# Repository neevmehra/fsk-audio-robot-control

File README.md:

# FSK Audio-Based Robot Control System

Real-time embedded communication system that transmits joystick commands over an acoustic channel using frequency shift keying (FSK), decodes received audio with ADC sampling and DFT-based frequency detection, and controls an RSLK robot.

## Overview

This project implements a wireless audio command system using two TM4C123 microcontrollers. The transmitter reads joystick input, maps each direction to a command, encodes the command into an audio signal, and outputs the waveform through a DAC and speaker. The receiver captures the transmitted signal through a microphone, samples it using an ADC, detects the dominant frequency, and drives an RSLK robot based on the decoded command.

The system was designed to operate in real time while remaining robust to noise and signal distortion in the acoustic channel.

## Features

* Joystick-controlled robot movement
* Acoustic command transmission using FSK tones
* DAC-generated sine wave output through speaker
* Microphone and ADC-based audio capture
* DFT-based frequency detection for command decoding
* FIFO buffering for real-time sample processing
* Interrupt-driven ADC sampling
* Stability filtering and thresholding for noise-tolerant decoding
* RSLK robot control for forward, backward, left, right, and stop commands

## System Architecture

1. Joystick input is read by the transmitter microcontroller.
2. The joystick direction is mapped to a command.
3. The command is encoded as an FSK audio tone.
4. The DAC generates the waveform and outputs it through a speaker.
5. The receiver microphone captures the transmitted audio.
6. The ADC samples the received signal.
7. A DFT-based decoder identifies the dominant frequency.
8. The decoded command is sent to the RSLK robot motor-control logic.

## Communication Protocol

The system uses frequency shift keying to represent command data as distinct audio tones. Each command is transmitted over the air through a speaker and decoded by identifying the dominant received frequency.

The receiver performs frequency-domain analysis using DFT magnitude calculations across expected command frequencies. Thresholding and stability checks help reject transient noise and prevent incorrect command execution.

## Technical Implementation

### Transmitter

* Reads joystick position using ADC inputs
* Applies directional mapping and deadband logic
* Converts commands into encoded audio tones
* Generates sine wave samples using a lookup table
* Outputs audio through a DAC and speaker circuit

### Receiver

* Samples microphone input using interrupt-driven ADC logic
* Removes DC offset from sampled audio
* Buffers samples using FIFO structures
* Computes DFT magnitudes for target frequencies
* Selects the dominant frequency based on magnitude and threshold checks
* Uses stability filtering before executing robot commands

### Robot Control

* Decoded commands control RSLK robot movement
* Supported commands include forward, backward, left, right, and stop
* The system runs within real-time constraints with sufficient CPU timing margin

## Hardware

* TM4C123 microcontrollers
* RSLK robot platform
* Joystick input module
* DAC output circuit
* Speaker
* Microphone receiver circuit
* Breadboarded analog interface circuitry
* Oscilloscope for waveform validation

## Software

* Embedded C
* Interrupt-driven ADC sampling
* DAC waveform generation
* FIFO buffering
* DFT-based frequency detection
* Command decoding and robot-control logic

## Testing

The system was tested at both the module and integration levels.

### Unit Testing

* Verified DAC sine wave output using oscilloscope traces
* Tested joystick ADC readings and command mapping
* Validated microphone ADC sampling
* Tested DFT frequency detection using known input tones
* Checked frame parsing and command decoding logic

### Integration Testing

* Verified end-to-end joystick-to-robot command transmission
* Tested real-time robot response to live joystick input
* Evaluated noise tolerance under background audio interference
* Measured communication reliability over increasing speaker-to-microphone distance
* Confirmed timing performance under real-time sampling constraints

## Results

* Successfully transmitted joystick commands over an acoustic channel
* Controlled an RSLK robot using decoded audio commands
* Maintained reliable command detection using DFT-based decoding
* Demonstrated real-time operation with interrupt-driven sampling and FIFO buffering
* Operated with tolerance to moderate environmental noise

## Repository Structure

```text
.
├── README.md
├── sw/                  # Embedded software
├── hw/                  # Hardware design files
├── Resources/           # Supporting resources
└── docs/                # Lab report and documentation
```

## Project Context

This project was completed for ECE445L and focused on real-time embedded systems, digital signal processing, hardware/software integration, and robotics control.

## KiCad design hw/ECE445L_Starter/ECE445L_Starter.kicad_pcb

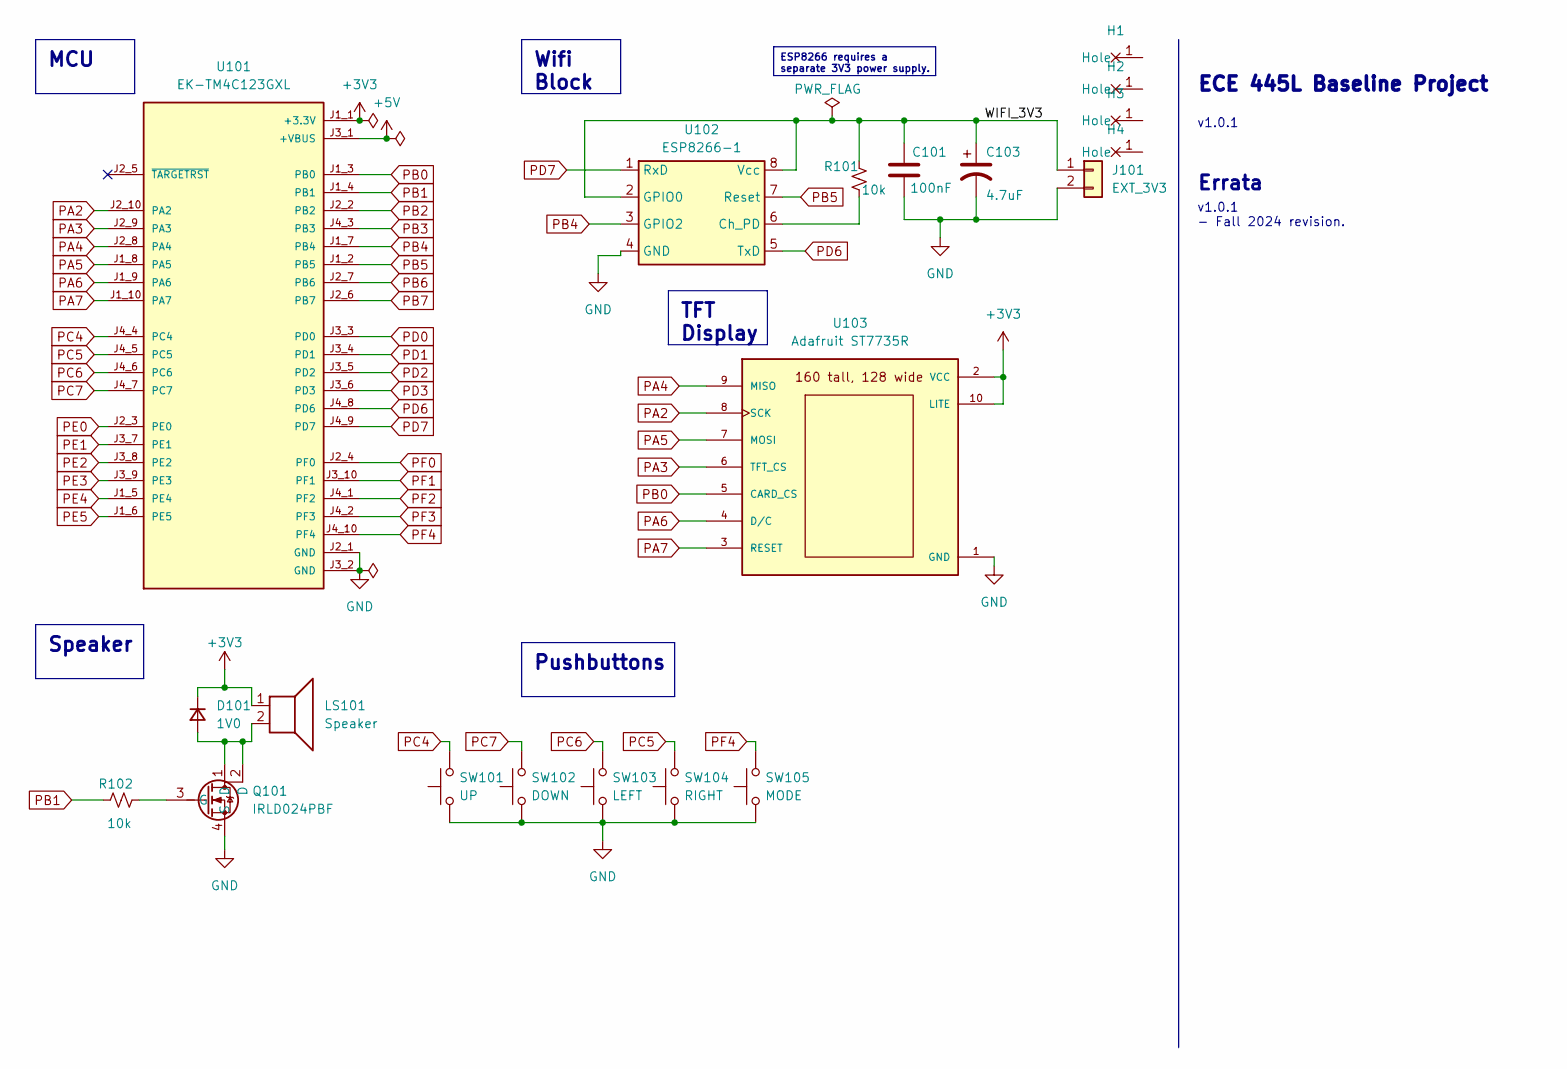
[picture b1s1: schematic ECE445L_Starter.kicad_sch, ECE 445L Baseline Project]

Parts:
C101: 100nF; C_Axial_200mil
C103: 4.7uF; CP_Radial_Tantal200mil
D101: 1V0; D_5W_P12.70mm_Horizontal
H1, H2, H3, H4: MountingHole_4_40
J101: EXT_3V3; Samtec_HPM-02-01-x-S_Straight_1x02_Pitch5.08mm
LS101: Speaker; PinHeader_1x02_P2.54mm_Vertical
Q101: IRLD024PBF; DIP920W60P254L490H457Q4N; Mouser Part Number 844-IRLD024PBF
R101, R102: 10k; R_Axial_DIN0204_L3.6mm_D1.6mm_P7.62mm_Horizontal
SW101: UP; SW_PUSH_6mm
SW102: DOWN; SW_PUSH_6mm
SW103: LEFT; SW_PUSH_6mm
SW104: RIGHT; SW_PUSH_6mm
SW105: MODE; SW_PUSH_6mm
U101: EK-TM4C123GXL; ti_EKTM4C123GXL
U102: ESP8266-1; PinHeader_2x04_P2.54mm_Vertical
U103: Adafruit ST7735R; adafruit_st7735r2

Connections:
+3V3: D101.1 (K), LS101.1, U101.J1_1 (+3.3V), U103.2 (VCC), U103.10 (LITE)
+5V: U101.J3_1 (+VBUS)
/WIFI_3V3: C101.1, C103.1, J101.1, R101.1, U102.2 (GPIO0), U102.8 (Vcc)
GND: C101.2, C103.2, J101.2, Q101.4 (S), SW101.1, SW102.1, SW103.1, SW104.1, SW105.1, U101.J2_1 (GND), U101.J3_2 (GND), U102.4 (GND), U103.1 (GND)
unnamed: D101.2 (A), LS101.2, Q101.1 (D), Q101.2 (D)
unnamed: Q101.3 (G), R102.2
unnamed: R101.2, U102.6 (Ch_PD)
PA2: U101.J2_10 (PA2), U103.8 (SCK)
PA3: U101.J2_9 (PA3), U103.6 (TFT_CS)
PA4: U101.J2_8 (PA4), U103.9 (MISO)
PA5: U101.J1_8 (PA5), U103.7 (MOSI)
PA6: U101.J1_9 (PA6), U103.4 (D/C)
PA7: U101.J1_10 (PA7), U103.3 (RESET)
PB0: U101.J1_3 (PB0), U103.5 (CARD_CS)
PB1: R102.1, U101.J1_4 (PB1)
PB2: U101.J2_2 (PB2)
PB3: U101.J4_3 (PB3)
PB4: U101.J1_7 (PB4), U102.3 (GPIO2)
PB5: U101.J1_2 (PB5), U102.7 (Reset)
PB6: U101.J2_7 (PB6)
PB7: U101.J2_6 (PB7)
PC4: SW101.2, U101.J4_4 (PC4)
PC5: SW104.2, U101.J4_5 (PC5)
PC6: SW103.2, U101.J4_6 (PC6)
PC7: SW102.2, U101.J4_7 (PC7)
PD0: U101.J3_3 (PD0)
PD1: U101.J3_4 (PD1)
PD2: U101.J3_5 (PD2)
PD3: U101.J3_6 (PD3)
PD6: U101.J4_8 (PD6), U102.5 (TxD)
PD7: U101.J4_9 (PD7), U102.1 (RxD)
PE0: U101.J2_3 (PE0)
PE1: U101.J3_7 (PE1)
PE2: U101.J3_8 (PE2)
PE3: U101.J3_9 (PE3)
PE4: U101.J1_5 (PE4)
PE5: U101.J1_6 (PE5)
PF0: U101.J2_4 (PF0)
PF1: U101.J3_10 (PF1)
PF2: U101.J4_1 (PF2)
PF3: U101.J4_2 (PF3)
PF4: SW105.2, U101.J4_10 (PF4)

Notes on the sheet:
MCU
ESP8266 requires a separate 3V3 power supply.
Speaker
Pushbuttons
TFT Display
Wifi Block
v1.0.1 - Fall 2024 revision.
ECE 445L Baseline Project
v1.0.1
Errata

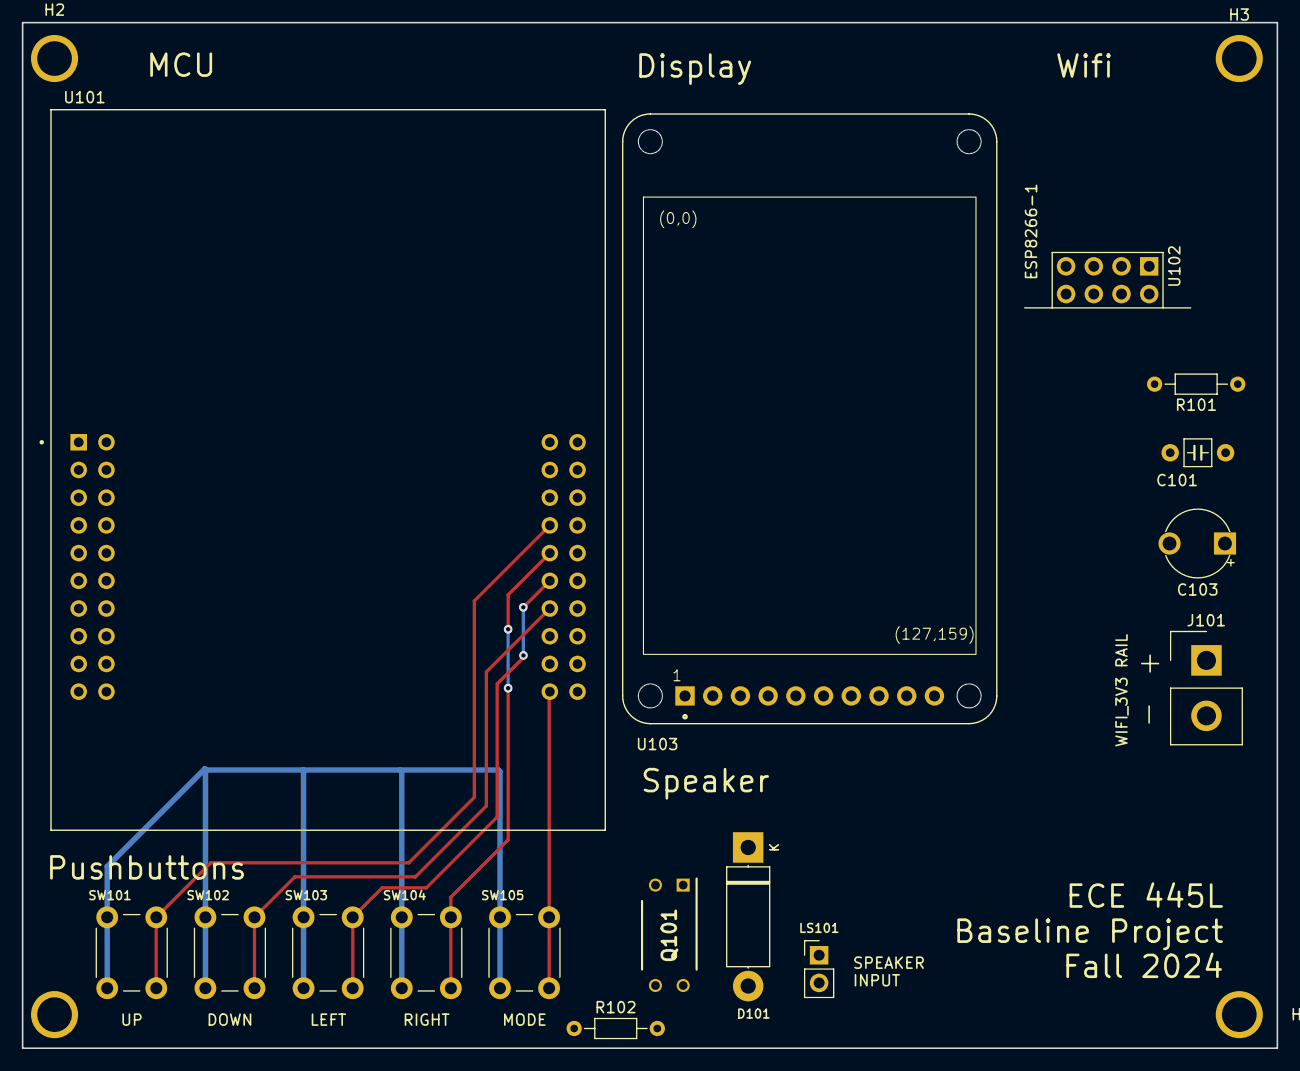
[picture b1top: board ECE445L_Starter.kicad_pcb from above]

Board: 2 copper layers, 115.0 x 94.0 mm, 20 parts (0 on the bottom side), 23 nets.

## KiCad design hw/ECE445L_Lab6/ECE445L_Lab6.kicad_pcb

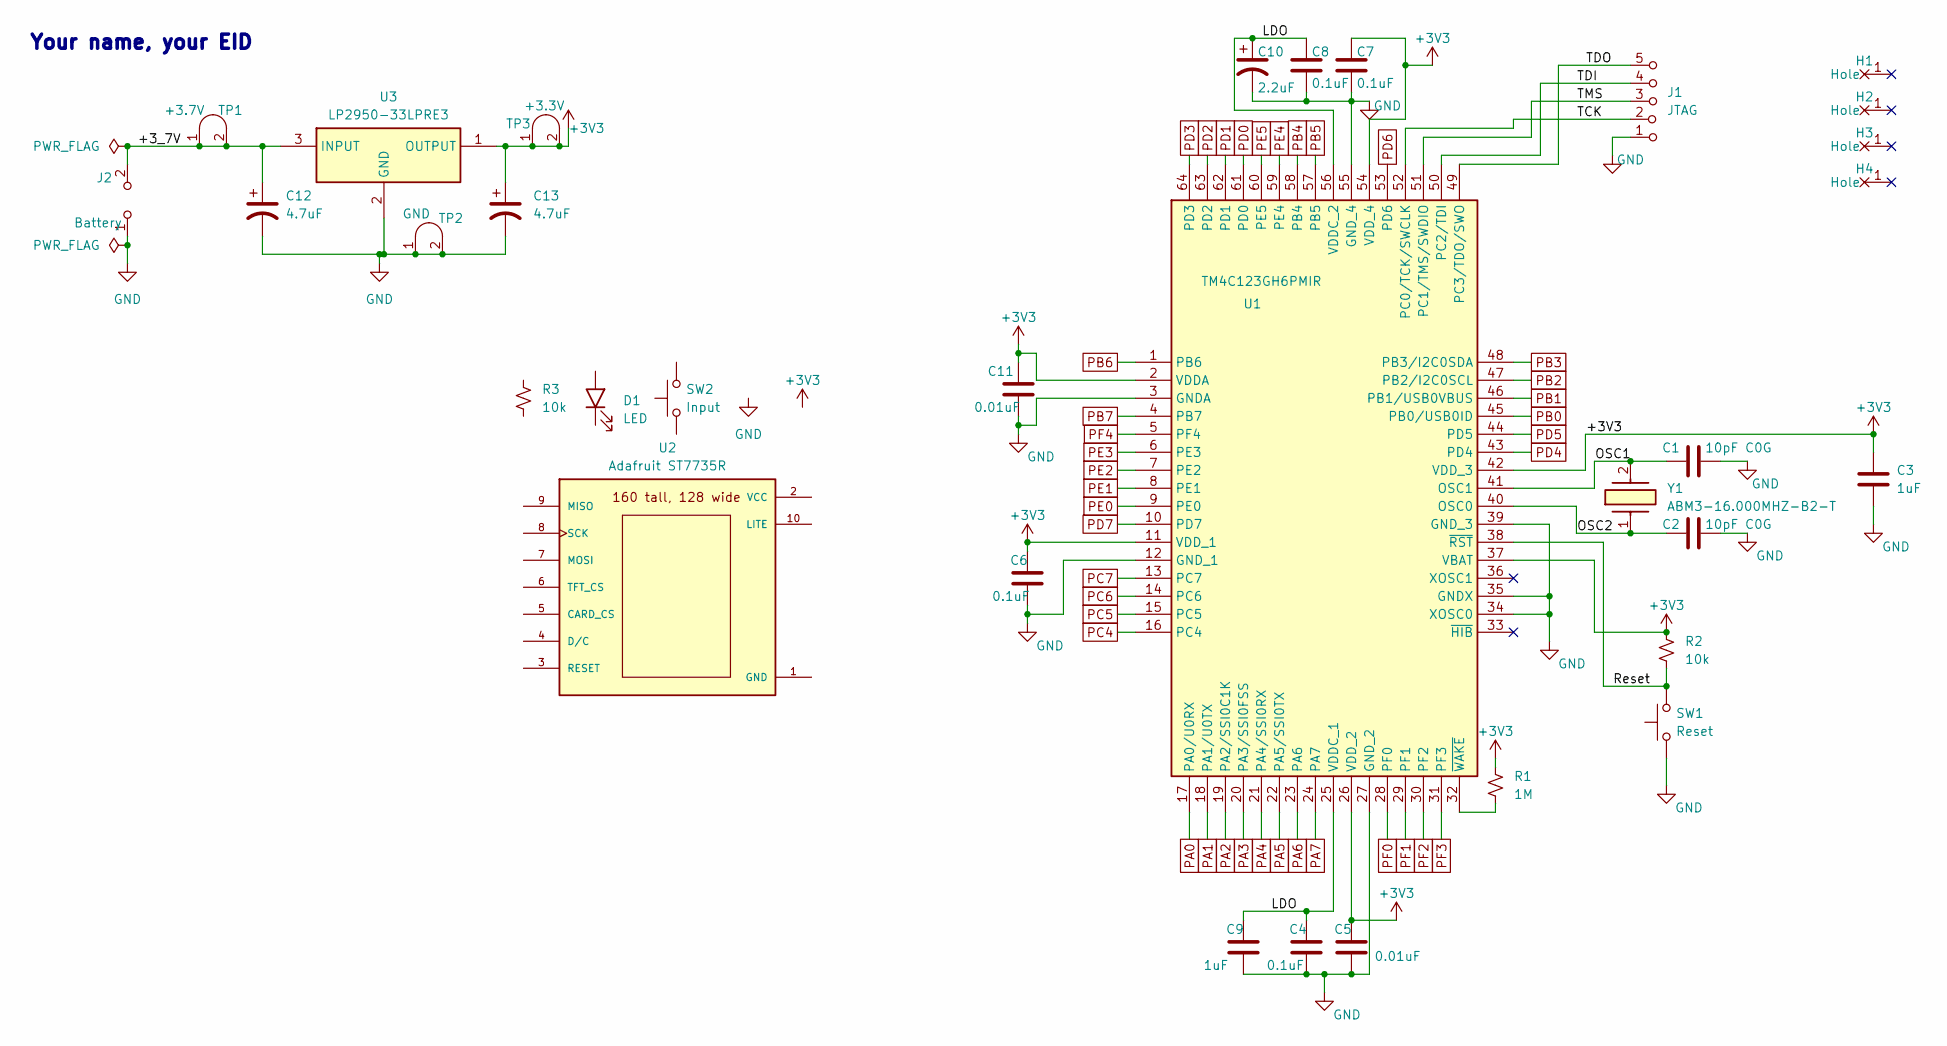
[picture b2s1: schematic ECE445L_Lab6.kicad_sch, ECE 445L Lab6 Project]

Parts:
C1, C2: 10pF C0G; C_Axial_200mil
C3, C9: 1uF; C_Axial_200mil
C4, C6, C7, C8: 0.1uF; C_Axial_200mil
C5, C11: 0.01uF; C_Axial_200mil
C10: 2.2uF; CP_Radial_Tantal200mil
C12, C13: 4.7uF; CP_Radial_Tantal200mil
D1: LED; LED_D5.0mm
H1, H2, H3, H4: MountingHole_4_40
J1: JTAG; PinHeader_1x05_P2.54mm_Vertical
J2: Battery; PinHeader_1x02_P2.54mm_Vertical
R1: 1M; R_Axial_DIN0204_L3.6mm_D1.6mm_P7.62mm_Horizontal
R2, R3: 10k; R_Axial_DIN0204_L3.6mm_D1.6mm_P7.62mm_Horizontal
SW1: Reset; SW_PUSH_6mm
SW2: Input; SW_PUSH_6mm
TP1: +3.7V; Testpoint_1x02_P2.54mm
TP2: GND; Testpoint_1x02_P2.54mm
TP3: +3.3V; Testpoint_1x02_P2.54mm
U1: TM4C123GH6PMIR; QFP50P1200X1200X160-64N; Mouser Part Number 595-TM4C123GH6PMIR
U2: Adafruit ST7735R; adafruit_st7735r2
U3: LP2950-33LPRE3; TL431CLPM; Mouser Part Number 595-LP2950-33LPRE3
Y1: ABM3-16.000MHZ-B2-T; ABM3; Mouser Part Number 815-ABM3-16-B2-T

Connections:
+3V3: C3.1, C5.1, C6.1, C7.1, C11.1, C13.1, R1.1, R2.1, TP3.1 (A), TP3.2 (B), U1.2 (VDDA), U1.11 (VDD_1), U1.26 (VDD_2), U1.37 (VBAT), U1.42 (VDD_3), U1.54 (VDD_4), U3.1 (OUTPUT)
/+3_7V: C12.1, J2.2 (B), TP1.1 (A), TP1.2 (B), U3.3 (INPUT)
/LDO: C4.1, C8.1, C9.1, C10.1, U1.25 (VDDC_1), U1.56 (VDDC_2)
/OSC1: C1.1, U1.41 (OSC1), Y1.2
/OSC2: C2.1, U1.40 (OSC0), Y1.1
/Reset: R2.2, SW1.2, U1.38 (~RST)
/TCK: J1.2 (B), U1.52 (PC0/TCK/SWCLK)
/TDI: J1.4 (C), U1.50 (PC2/TDI)
/TDO: J1.5 (C), U1.49 (PC3/TDO/SWO)
/TMS: J1.3 (C), U1.51 (PC1/TMS/SWDIO)
GND: C1.2, C2.2, C3.2, C4.2, C5.2, C6.2, C7.2, C8.2, C9.2, C10.2, C11.2, C12.2, C13.2, J1.1 (A), J2.1 (A), SW1.1, TP2.1 (A), TP2.2 (B), U1.3 (GNDA), U1.12 (GND_1), U1.27 (GND_2), U1.34 (XOSC0), U1.35 (GNDX), U1.39 (GND_3), U1.55 (GND_4), U3.2 (GND)
unnamed: R1.2, U1.32 (~WAKE)
PA0: U1.17 (PA0/U0RX)
PA1: U1.18 (PA1/U0TX)
PA2: U1.19 (PA2/SSI0C1K)
PA3: U1.20 (PA3/SSI0FSS)
PA4: U1.21 (PA4/SSI0RX)
PA5: U1.22 (PA5/SSI0TX)
PA6: U1.23 (PA6)
PA7: U1.24 (PA7)
PB0: U1.45 (PB0/USB0ID)
PB1: U1.46 (PB1/USB0VBUS)
PB2: U1.47 (PB2/I2C0SCL)
PB3: U1.48 (PB3/I2C0SDA)
PB4: U1.58 (PB4)
PB5: U1.57 (PB5)
PB6: U1.1 (PB6)
PB7: U1.4 (PB7)
PC4: U1.16 (PC4)
PC5: U1.15 (PC5)
PC6: U1.14 (PC6)
PC7: U1.13 (PC7)
PD0: U1.61 (PD0)
PD1: U1.62 (PD1)
PD2: U1.63 (PD2)
PD3: U1.64 (PD3)
PD4: U1.43 (PD4)
PD5: U1.44 (PD5)
PD6: U1.53 (PD6)
PD7: U1.10 (PD7)
PE0: U1.9 (PE0)
PE1: U1.8 (PE1)
PE2: U1.7 (PE2)
PE3: U1.6 (PE3)
PE4: U1.59 (PE4)
PE5: U1.60 (PE5)
PF0: U1.28 (PF0)
PF1: U1.29 (PF1)
PF2: U1.30 (PF2)
PF3: U1.31 (PF3)
PF4: U1.5 (PF4)

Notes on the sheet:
Your name, your EID

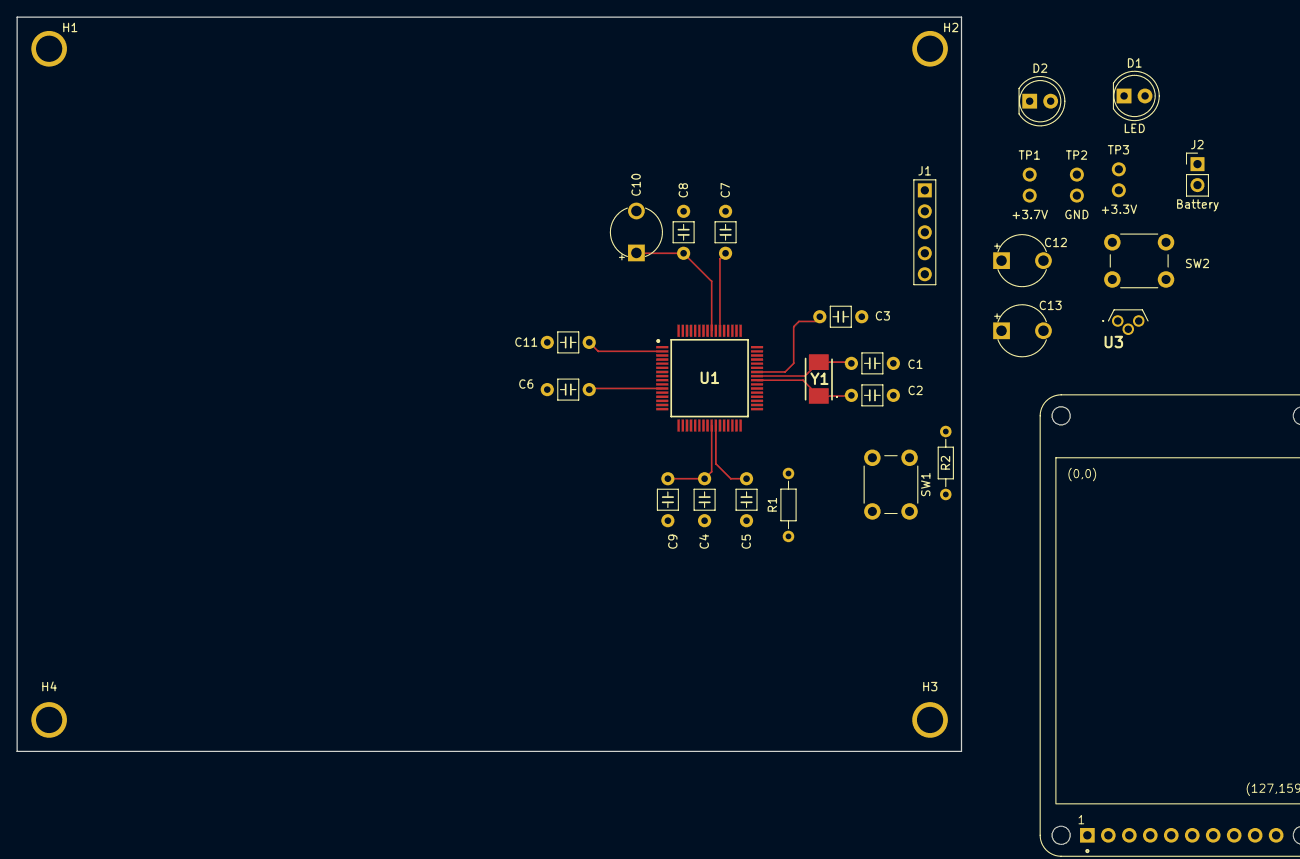
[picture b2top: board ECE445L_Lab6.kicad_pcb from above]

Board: 2 copper layers, 114.4 x 88.9 mm, 32 parts (0 on the bottom side), 12 nets.

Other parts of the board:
D2: LED; LED_D5.0mm

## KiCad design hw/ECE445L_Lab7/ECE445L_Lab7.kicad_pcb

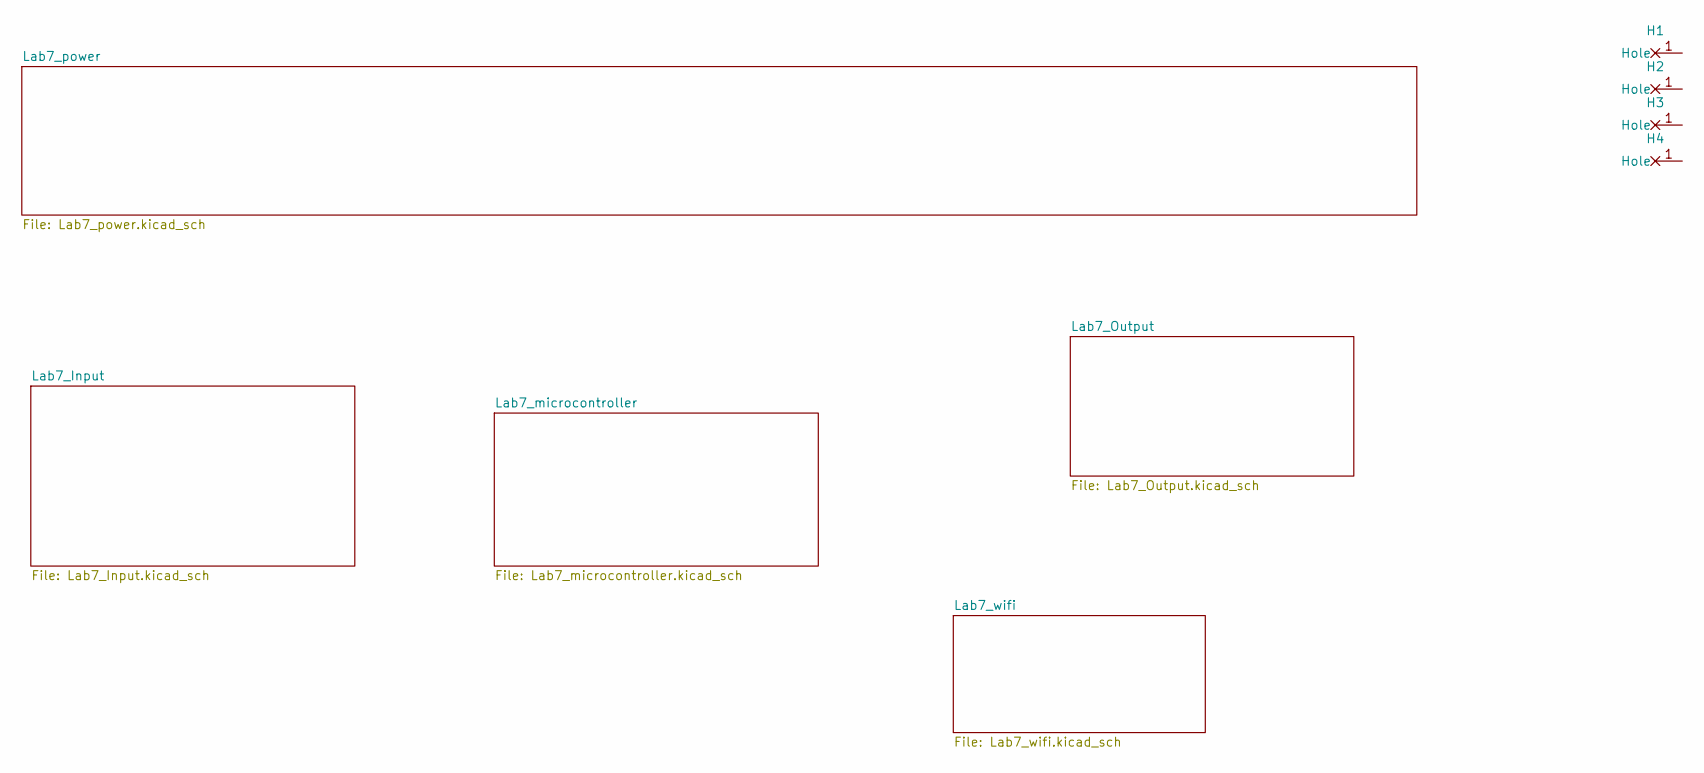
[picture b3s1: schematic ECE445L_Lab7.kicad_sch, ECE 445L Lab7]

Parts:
H1, H2, H3, H4: MountingHole_4_40

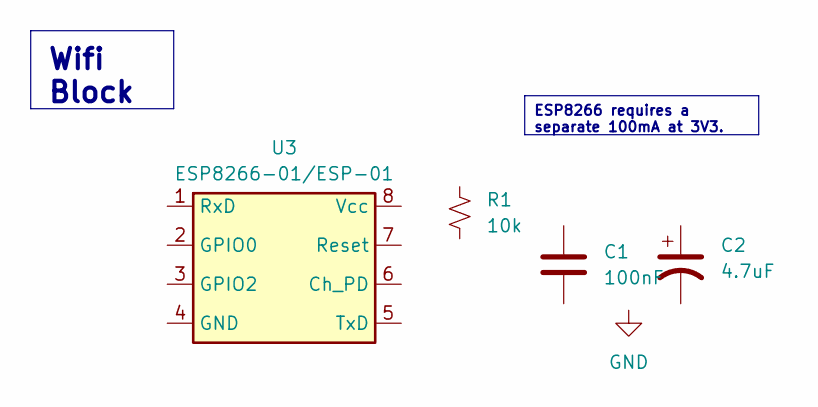
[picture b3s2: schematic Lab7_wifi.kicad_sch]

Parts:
C1: 100nF; C_Axial_200mil
C2: 4.7uF; CP_Radial_Tantal200mil
R1: 10k; R_Axial_DIN0204_L3.6mm_D1.6mm_P7.62mm_Horizontal
U3: ESP8266-01/ESP-01; PinHeader_2x04_P2.54mm_Vertical

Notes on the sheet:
ESP8266 requires a separate 100mA at 3V3.
Wifi Block

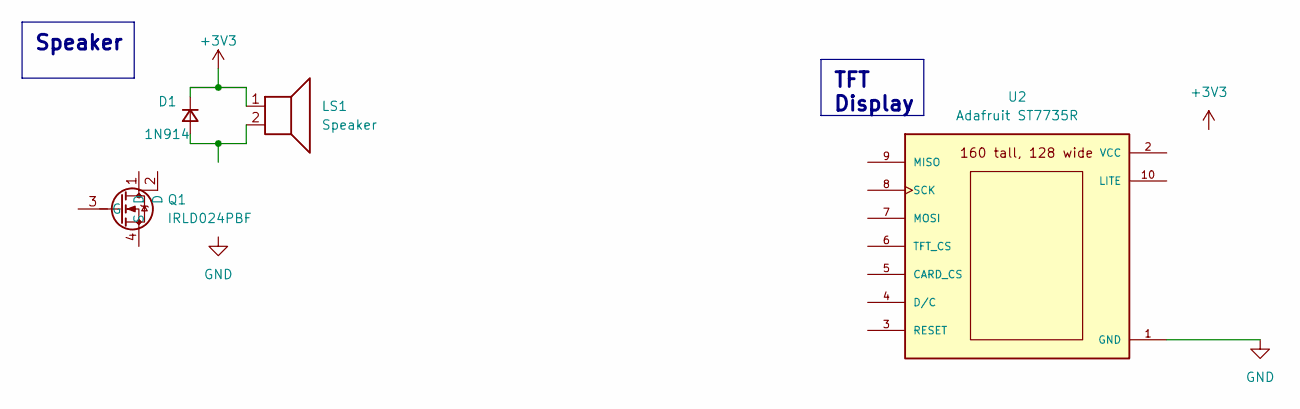
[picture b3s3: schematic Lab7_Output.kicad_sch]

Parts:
D1: 1N914; D_P6.35mm_Horizontal
LS1: Speaker; PinHeader_1x02_P2.54mm_Vertical
Q1: IRLD024PBF; DIP920W60P254L490H457Q4N; Mouser Part Number 844-IRLD024PBF
U2: Adafruit ST7735R; adafruit_st7735r2

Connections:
+3V3: D1.1 (K), LS1.1; also elsewhere on the board
GND: U2.1 (GND); also elsewhere on the board
unnamed: D1.2 (A), LS1.2

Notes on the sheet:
TFT Display
Speaker

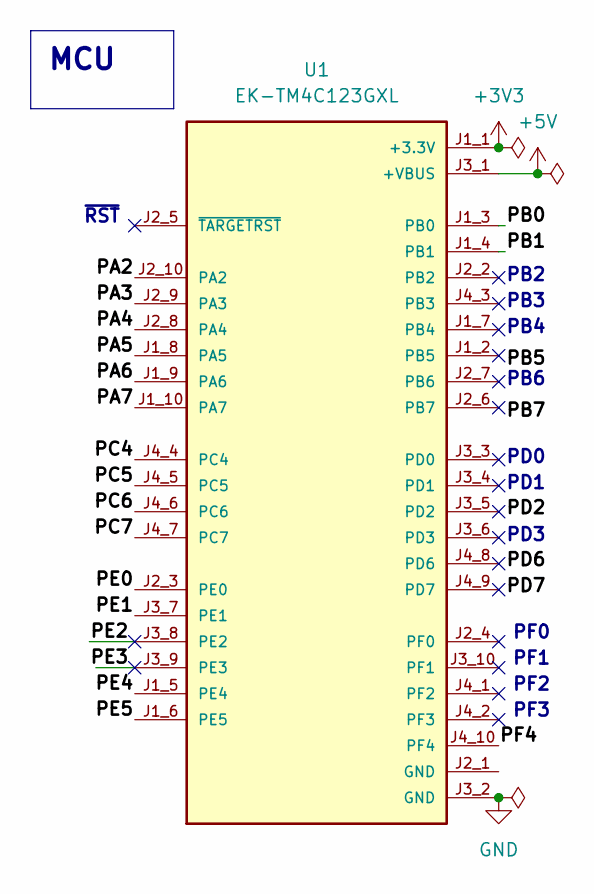
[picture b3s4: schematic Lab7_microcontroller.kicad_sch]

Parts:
U1: EK-TM4C123GXL; ti_EKTM4C123GXL

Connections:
+3V3: U1.J1_1 (+3.3V); also elsewhere on the board
+5V: U1.J3_1 (+VBUS)
/Lab7_microcontroller/PA2: U1.J2_10 (PA2)
/Lab7_microcontroller/PA3: U1.J2_9 (PA3)
/Lab7_microcontroller/PA4: U1.J2_8 (PA4)
/Lab7_microcontroller/PA5: U1.J1_8 (PA5)
/Lab7_microcontroller/PA6: U1.J1_9 (PA6)
/Lab7_microcontroller/PA7: U1.J1_10 (PA7)
/Lab7_microcontroller/PB0: U1.J1_3 (PB0)
/Lab7_microcontroller/PB1: U1.J1_4 (PB1)
/Lab7_microcontroller/PC4: U1.J4_4 (PC4)
/Lab7_microcontroller/PC5: U1.J4_5 (PC5)
/Lab7_microcontroller/PC6: U1.J4_6 (PC6)
/Lab7_microcontroller/PC7: U1.J4_7 (PC7)
/Lab7_microcontroller/PE0: U1.J2_3 (PE0)
/Lab7_microcontroller/PE1: U1.J3_7 (PE1)
/Lab7_microcontroller/PE2: U1.J3_8 (PE2)
/Lab7_microcontroller/PE4: U1.J1_5 (PE4)
/Lab7_microcontroller/PE5: U1.J1_6 (PE5)
/Lab7_microcontroller/PF4: U1.J4_10 (PF4)
GND: U1.J3_2 (GND); also elsewhere on the board

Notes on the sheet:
MCU
~{RST}
PB2
PD3
PF3
PB3
PB4
PD1
PF1
PB6
PD0
PF2
PF0

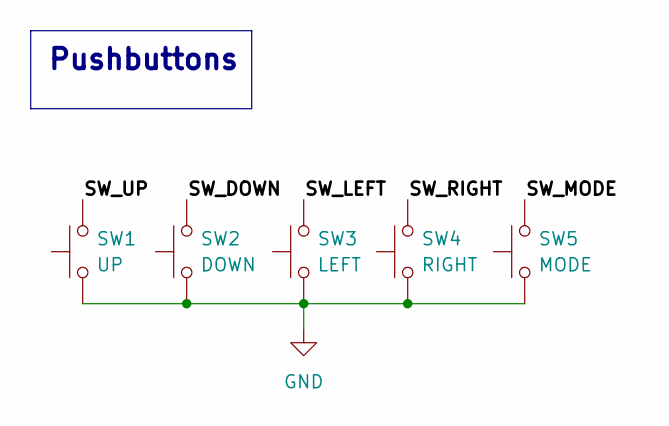
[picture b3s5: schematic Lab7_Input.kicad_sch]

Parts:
SW1: UP; SW_PUSH_6mm
SW2: DOWN; SW_PUSH_6mm
SW3: LEFT; SW_PUSH_6mm
SW4: RIGHT; SW_PUSH_6mm
SW5: MODE; SW_PUSH_6mm

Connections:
/Lab7_Input/SW_DOWN: SW2.2
/Lab7_Input/SW_LEFT: SW3.2
/Lab7_Input/SW_MODE: SW5.2
/Lab7_Input/SW_RIGHT: SW4.2
/Lab7_Input/SW_UP: SW1.2
GND: SW1.1, SW2.1, SW3.1, SW4.1, SW5.1; also elsewhere on the board

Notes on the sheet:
Pushbuttons

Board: 2 copper layers, 18 parts (0 on the bottom side), 3 nets, no tracks yet.

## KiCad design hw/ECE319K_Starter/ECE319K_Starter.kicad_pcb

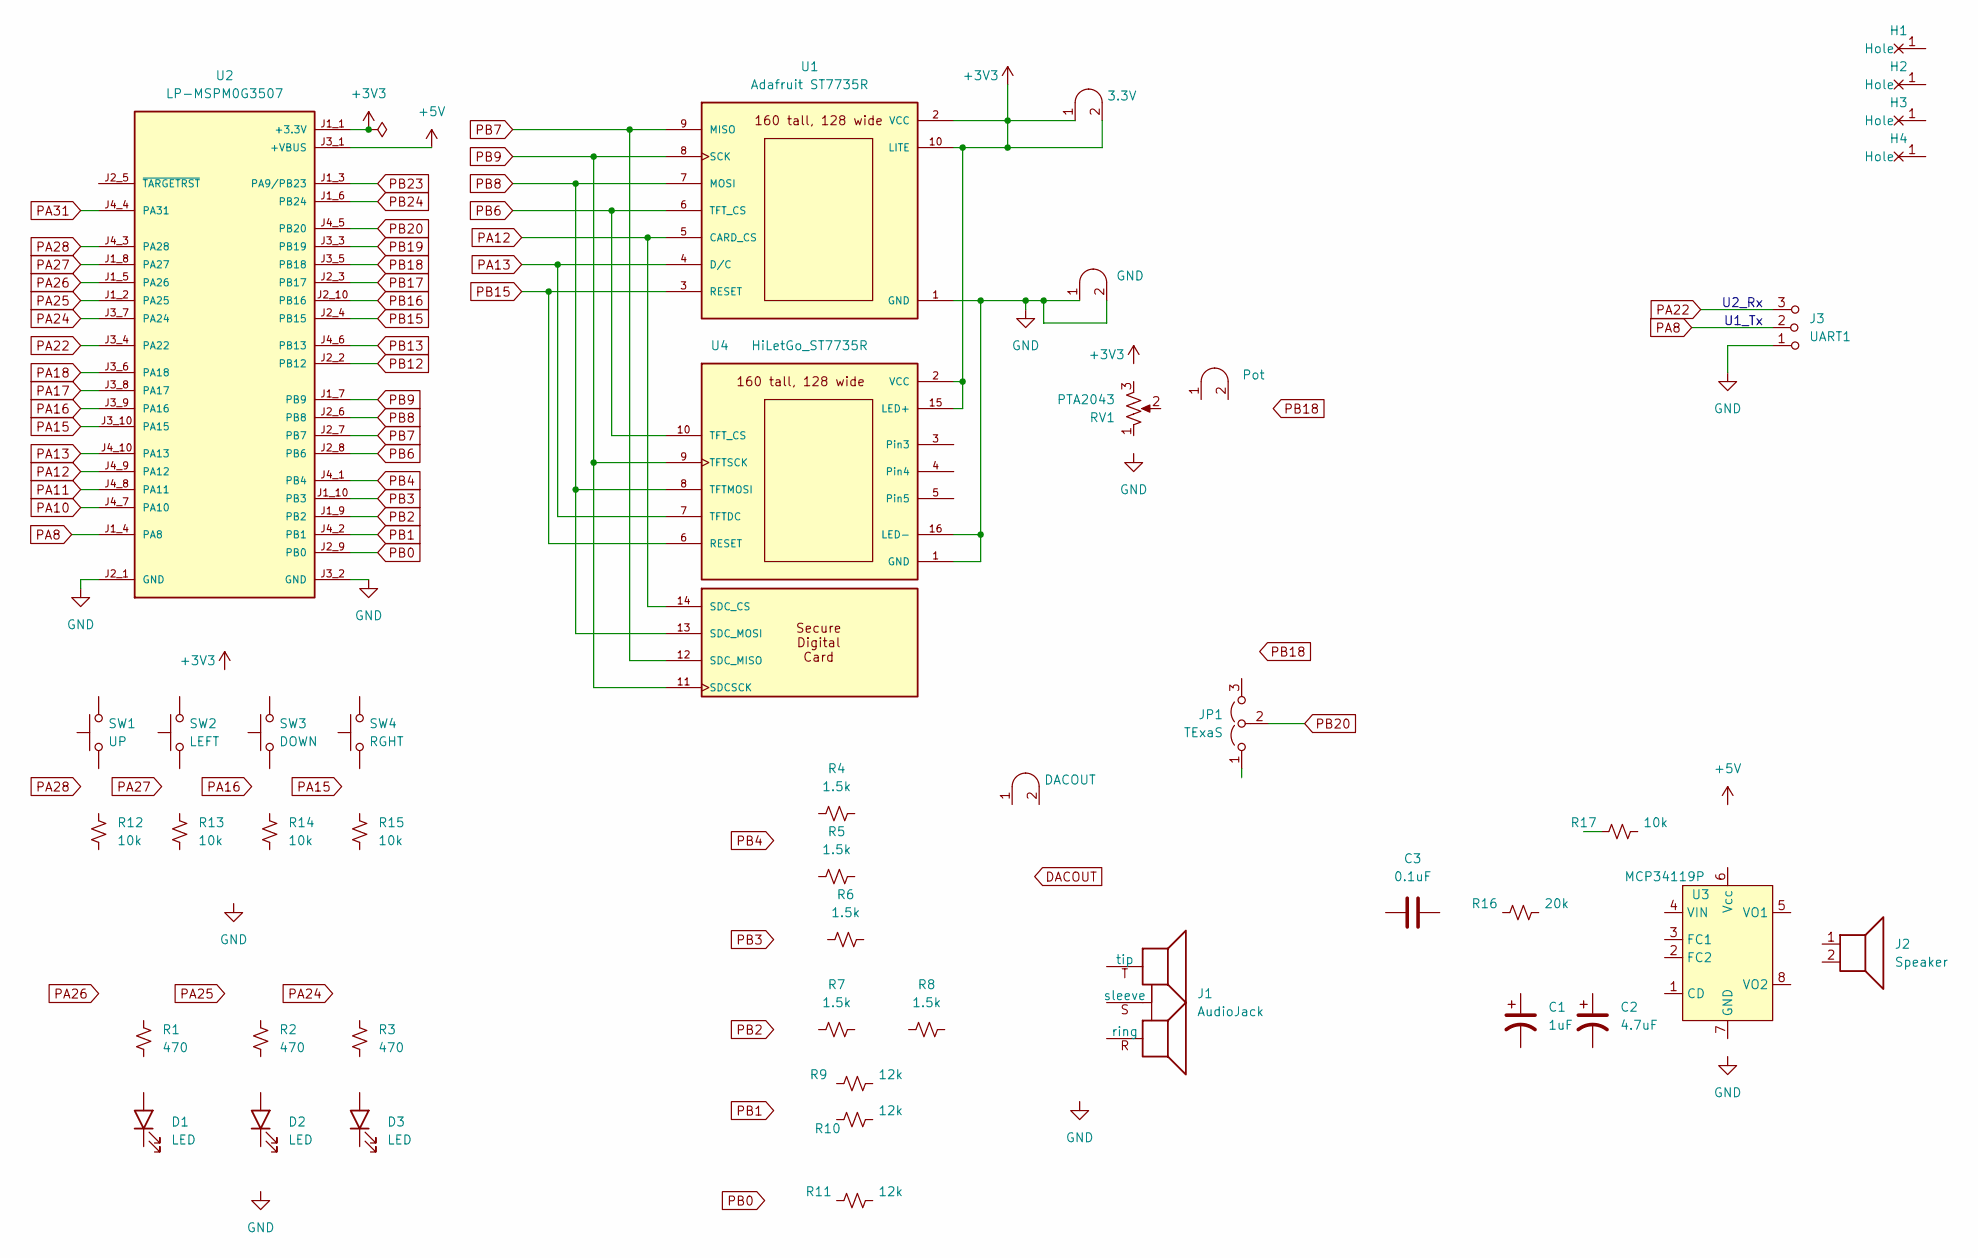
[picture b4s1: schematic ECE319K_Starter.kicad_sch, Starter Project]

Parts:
C1: 1uF; CP_Radial_Tantal200mil
C2: 4.7uF; CP_Radial_Tantal200mil
C3: 0.1uF; C_Axial_200mil
D1, D2, D3: LED; LED_D5.0mm
H1, H2, H3, H4: MountingHole_4_40
J1: AudioJack; Jack_3.5mm_CUI_SJ1-3523N_Horizontal
J2: Speaker; PinHeader_1x02_P2.54mm_Vertical
J3: UART1; PinHeader_1x03_P2.54mm_Vertical
J4: Pot; Testpoint_1x02_P2.54mm
J6: GND; Testpoint_1x02_P2.54mm
J7: DACOUT; Testpoint_1x02_P2.54mm
JP1: TExaS; PinHeader_1x03_P2.54mm_Vertical
R1, R2, R3: 470; R_Axial_DIN0204_L3.6mm_D1.6mm_P7.62mm_Horizontal
R4, R5, R6, R7, R8: 1.5k; R_Axial_DIN0204_L3.6mm_D1.6mm_P7.62mm_Horizontal
R9, R10, R11: 12k; R_Axial_DIN0204_L3.6mm_D1.6mm_P7.62mm_Horizontal
R12, R13, R14, R15, R17: 10k; R_Axial_DIN0204_L3.6mm_D1.6mm_P7.62mm_Horizontal
R16: 20k; R_Axial_DIN0204_L3.6mm_D1.6mm_P7.62mm_Horizontal
RV1: PTA2043; PTA2043pot
SW1: UP; SW_PUSH_6mm
SW2: LEFT; SW_PUSH_6mm
SW3: DOWN; SW_PUSH_6mm
SW4: RGHT; SW_PUSH_6mm
TP1: 3.3V; Testpoint_1x02_P2.54mm
U1: Adafruit ST7735R; adafruit_st7735r2
U2: LP-MSPM0G3507; ti_LP_MSPM0G3507
U3: MCP34119P; DIP-8_W7.62mm_LongPads
U4: HiLetGo_ST7735R; hiletgo_st7735r

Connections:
+3V3: TP1.1 (A), TP1.2 (B), U1.2 (VCC), U1.10 (LITE), U2.J1_1 (+3.3V), U4.2 (VCC), U4.15 (LED+)
+5V: U2.J3_1 (+VBUS)
GND: J3.1 (A), J6.1 (A), J6.2 (B), U1.1 (GND), U2.J2_1 (GND), U2.J3_2 (GND), U4.1 (GND), U4.16 (LED-)
PA8: J3.2 (B), U2.J1_4 (PA8)
PA10: U2.J4_7 (PA10)
PA11: U2.J4_8 (PA11)
PA12: U1.5 (CARD_CS), U2.J4_9 (PA12), U4.14 (SDC_CS)
PA13: U1.4 (D/C), U2.J4_10 (PA13), U4.7 (TFTDC)
PA15: U2.J3_10 (PA15)
PA16: U2.J3_9 (PA16)
PA17: U2.J3_8 (PA17)
PA18: U2.J3_6 (PA18)
PA22: J3.3 (C), U2.J3_4 (PA22)
PA24: U2.J3_7 (PA24)
PA25: U2.J1_2 (PA25)
PA26: U2.J1_5 (PA26)
PA27: U2.J1_8 (PA27)
PA28: U2.J4_3 (PA28)
PA31: U2.J4_4 (PA31)
PB0: U2.J2_9 (PB0)
PB1: U2.J4_2 (PB1)
PB2: U2.J1_9 (PB2)
PB3: U2.J1_10 (PB3)
PB4: U2.J4_1 (PB4)
PB6: U1.6 (TFT_CS), U2.J2_8 (PB6), U4.10 (TFT_CS)
PB7: U1.9 (MISO), U2.J2_7 (PB7), U4.12 (SDC_MISO)
PB8: U1.7 (MOSI), U2.J2_6 (PB8), U4.8 (TFTMOSI), U4.13 (SDC_MOSI)
PB9: U1.8 (SCK), U2.J1_7 (PB9), U4.9 (TFTSCK), U4.11 (SDCSCK)
PB12: U2.J2_2 (PB12)
PB13: U2.J4_6 (PB13)
PB15: U1.3 (RESET), U2.J2_4 (PB15), U4.6 (RESET)
PB16: U2.J2_10 (PB16)
PB17: U2.J2_3 (PB17)
PB18: U2.J3_5 (PB18)
PB19: U2.J3_3 (PB19)
PB20: JP1.2 (C), U2.J4_5 (PB20)
PB23: U2.J1_3 (PA9/PB23)
PB24: U2.J1_6 (PB24)

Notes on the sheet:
U2_Rx
U1_Tx

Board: 2 copper layers, 44 parts (1 on the bottom side), 12 nets, no tracks yet.

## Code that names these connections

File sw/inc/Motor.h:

/*!
 * @defgroup RSLK
 * @brief RSLK motor interface
 <table>
<caption id="RSLKmotor pins">RSLK motor pins</caption>
<tr><th> TM4C <th> MSPM0  <th> Description
<tr><td> PF2  <td> PB4  <td> Motor_PWML, ML+, IN3, PB.4/TIMA1_C0;
<tr><td> PF3  <td> PB1  <td> Motor_PWMR, MR+, IN1, PB.1/TIMA1_C1;
<tr><td> PA3  <td> PB0  <td> Motor_DIR_L,ML-, IN4, 1 means forward, 0 means backward
<tr><td> PA2  <td> PB16 <td> Motor_DIR_R,MR-, IN2
</table>
 * @{*/
/**
 * @file      Motor.h
 * @brief     RSLK dual H-bridge driver
 * @details   RSLK motor interface<br>

 * @version   RSLK v2.02
 * @author    Daniel Valvano and Jonathan Valvano
 * @copyright Copyright 2024 by Jonathan W. Valvano, valvano@mail.utexas.edu,
 * @warning   AS-IS
 * @note      For more information see  http://users.ece.utexas.edu/~valvano/
 * @date      July 1, 2024
 <table>
<caption id="RSLKmotor2">RSLK motor pins</caption>
<tr><th> TM4C <th> MSPM0  <th> Description
<tr><td> PF2  <td> PB4  <td> Motor_PWML, ML+, IN3, PWM M1PWM6
<tr><td> PF3  <td> PB1  <td> Motor_PWMR, MR+, IN1, PWM M1PWM7
<tr><td> PA3  <td> PB0  <td> Motor_DIR_L,ML-, IN4, GPIO, 0 means forward, 1 means backward
<tr><td> PA2  <td> PB16 <td> Motor_DIR_R,MR-, IN2, GPIO, 0 means forward, 1 means backward
</table>
  ******************************************************************************/


#ifndef __MOTOR_H__
#define __MOTOR_H__
#include <stdint.h>
#define MOTOR_PERIOD 40000 // 12.5*4=50ns, 2ms
#define MOTORMIN 2
#define MOTORMAX (MOTOR_PERIOD-2)
/**
 * Initialize RSLK motors
 * PWM clock set to 50ns (divide by 4)
 * @param none
 * @return none
 * @brief  Initialize motors
 * @note period is 2000 us
 */
void Motor_Init(void);

/**
 * Set RSLK motor power forward<br>
 * @param dutyLeft MOTORMIN to MOTORMAX
 * @param dutyRight MOTORMIN to MOTORMAX
 * @return none
 * @note period is 10000 us
 * @brief  Go forward
 */
void Motor_Forward(uint32_t dutyLeft, uint32_t dutyRight);

/**
 * Set RSLK motor power backward<br>
 * @param dutyLeft MOTORMIN to MOTORMAX
 * @param dutyRight MOTORMIN to MOTORMAX
 * @return none
 * @note period is 2000 us
 * @brief  Go backward
 */
void Motor_Backward(uint32_t dutyLeft, uint32_t dutyRight);

/**
 * Set RSLK motor power right turn<br>
 * @param dutyLeft MOTORMIN to MOTORMAX
 * @param dutyRight MOTORMIN to MOTORMAX
 * @return none
 * @note period is 2000 us
 * @brief  Turn right
 */
void Motor_Right(uint32_t dutyLeft, uint32_t dutyRight);

/**
 * Set RSLK motor power left turn<br>
 * @param dutyLeft MOTORMIN to MOTORMAX
 * @param dutyRight MOTORMIN to MOTORMAX
 * @return none
 * @note period is 2000 us
 * @brief Turn left
 */
void Motor_Left(uint32_t dutyLeft, uint32_t dutyRight);

#endif

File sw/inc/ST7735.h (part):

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// ST7735
// Backlight (pin 10) connected to +3.3 V
// MISO (pin 9) unconnected
// SCK (pin 8) connected to PA2 (SSI0Clk)
// MOSI (pin 7) connected to PA5 (SSI0Tx)
// TFT_CS (pin 6) connected to PA3 (SSI0Fss)
// CARD_CS (pin 5) unconnected
// Data/Command (pin 4) connected to PA6 (GPIO), high for data, low for command
// RESET (pin 3) connected to PA7 (GPIO)
// VCC (pin 2) connected to +3.3 V
// Gnd (pin 1) connected to ground

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// Silkscreen Label (SDC side up; LCD side down) - Connection
// VCC  - +3.3 V
// GND  - Ground
// !SCL - PA2 Sclk SPI clock from microcontroller to TFT or SDC
// !SDA - PA5 MOSI SPI data from microcontroller to TFT or SDC
// DC   - PA6 TFT data/command
// RES  - PA7 TFT reset
// CS   - PA3 TFT_CS, active low to enable TFT
// *CS  - (NC) SDC_CS, active low to enable SDC
// MISO - (NC) MISO SPI data from SDC to microcontroller
// SDA   (NC) I2C data for ADXL345 accelerometer
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// Silkscreen Label (SDC side up; LCD side down) - Connection
// VCC  - +3.3 V
// GND  - Ground
// !SCL - PA2 Sclk SPI clock from microcontroller to TFT or SDC
// !SDA - PA5 MOSI SPI data from microcontroller to TFT or SDC
// DC   - PA6 TFT data/command
// RES  - PA7 TFT reset
// CS   - PA3 TFT_CS, active low to enable TFT
// *CS  - (NC) SDC_CS, active low to enable SDC
// MISO - (NC) MISO SPI data from SDC to microcontroller
// X (NC) analog input X-axis from ADXL335 accelerometer
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// MOSI   (pin 13) SDC, MOSI
// MISO   (pin 12) SDC, MISO
// SCK    (pin 11) SDC, serial clock
// CS     (pin 10) TFT, PA3 (SSI0Fss)
// SCL    (pin 9)  TFT, SCK  PA2 (SSI0Clk)
// SDA    (pin 8)  TFT, MOSI PA5 (SSI0Tx)
// A0     (pin 7)  TFT, Data/Command PA6 (GPIO), high for data, low for command
// RESET  (pin 6)  TFT, to PA7 (GPIO)
// NC     (pins 3,4,5) not connected
// VCC    (pin 2)  connected to +3.3 V
// GND    (pin 1)  connected to ground
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
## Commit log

2026-04-06 Flatten
2026-04-09 add deadline
2026-04-10 New code added
2026-04-11 Added Transmitter Functionality
2026-04-11 Initial change for Seth
2026-04-12 One direction works
2026-04-12 new
    new
2026-04-13 Joystick working properly
2026-04-13 Receiver.c code updated for working implementation
2026-04-15 Added Unit Testing
2026-06-07 Clean repository structure

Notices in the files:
sw/inc/ST7735.h:
MIT license, all text above must be included in any redistribution
"Embedded Systems: Introduction to ARM Cortex M Microcontrollers",
ISBN: 978-1469998749, Jonathan Valvano, copyright (c) 2020
"Embedded Systems: Real Time Interfacing to ARM Cortex M Microcontrollers",
ISBN: 978-1463590154, Jonathan Valvano, copyright (c) 2020
"Embedded Systems: Real-Time Operating Systems for ARM Cortex-M Microcontrollers",
ISBN: 978-1466468863, Jonathan Valvano, copyright (c) 2020
Copyright 2020 by Jonathan W. Valvano, valvano@mail.utexas.edu
